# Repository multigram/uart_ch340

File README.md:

# uart_ch340
UART board using CH340C, designed with KiCAD

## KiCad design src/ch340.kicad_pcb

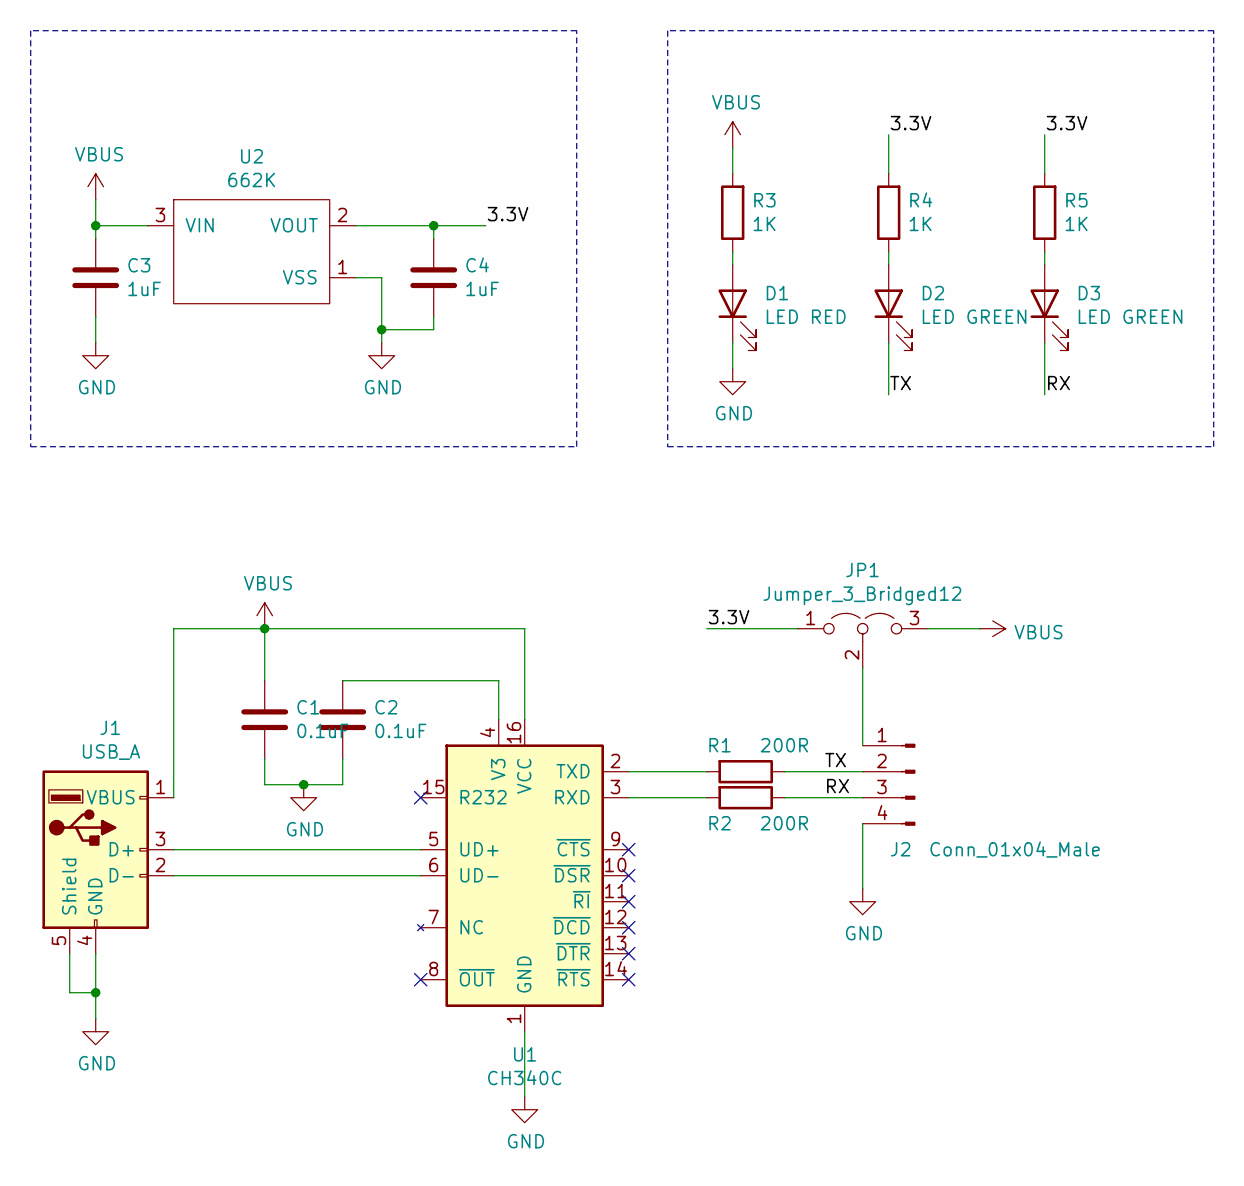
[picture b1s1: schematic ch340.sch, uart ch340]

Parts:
C1, C2: 0.1uF; C_0603_1608Metric_Pad1.08x0.95mm_HandSolder
C3, C4: 1uF; C_0603_1608Metric_Pad1.08x0.95mm_HandSolder
D1: LED RED; LED_0603_1608Metric_Pad1.05x0.95mm_HandSolder
D2, D3: LED GREEN; LED_0603_1608Metric_Pad1.05x0.95mm_HandSolder
J1: USB_A; USB_A_CNCTech_1001-011-01101_Horizontal
J2: Conn_01x04_Male; PinHeader_1x04_P2.54mm_Horizontal
JP1: Jumper_3_Bridged12; PinHeader_1x03_P2.54mm_Vertical
R1, R2: 200R; R_0603_1608Metric_Pad0.98x0.95mm_HandSolder
R3, R4, R5: 1K; R_0603_1608Metric_Pad0.98x0.95mm_HandSolder
U1: CH340C; SOIC-16_3.9x9.9mm_P1.27mm
U2: 662K; SOT-23_Handsoldering

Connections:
/3.3V: C4.1, JP1.1 (A), R4.2, R5.2, U2.2 (VOUT)
/RX: D3.1 (K), J2.3, R2.1
/TX: D2.1 (K), J2.2, R1.1
GND: C1.2, C2.2, C3.2, C4.2, D1.1 (K), J1.4 (GND), J1.5 (Shield), J2.4, U1.1 (GND), U2.1 (VSS)
unnamed: C2.1, U1.4 (V3)
unnamed: D1.2 (A), R3.1
unnamed: D2.2 (A), R4.1
unnamed: D3.2 (A), R5.1
unnamed: J1.2 (D-), U1.6 (UD-)
unnamed: J1.3 (D+), U1.5 (UD+)
unnamed: J2.1, JP1.2 (C)
unnamed: R1.2, U1.2 (TXD)
unnamed: R2.2, U1.3 (RXD)
VBUS: C1.1, C3.1, J1.1 (VBUS), JP1.3 (B), R3.2, U1.16 (VCC), U2.3 (VIN)

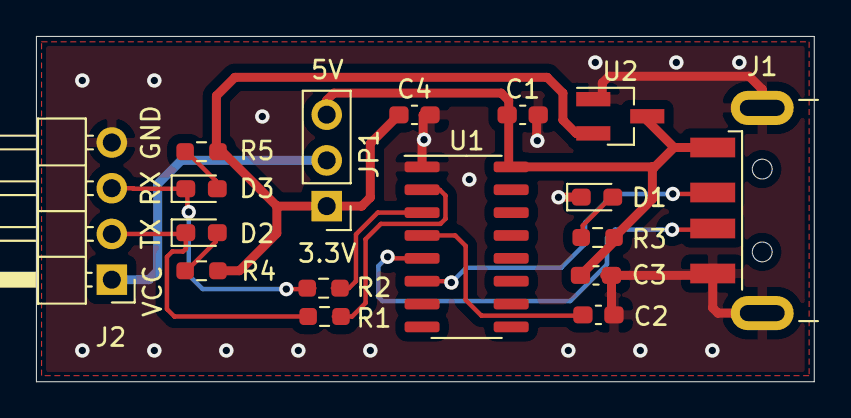
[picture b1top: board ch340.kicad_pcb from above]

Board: 2 copper layers, 43.2 x 19.2 mm, 17 parts (0 on the bottom side), 14 nets.

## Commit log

2021-06-05 add ch340c uart
2021-06-09 新增 led doc
2021-06-09 add doc/C72043_翠绿LED_2016-05-07.PDF
2021-06-18 1. set track width of GND, VCC 0.5mm 2. add vias to GND 3. change footprint, 0403 to 0603 handsoldering
2021-06-19 更新布线
2021-06-20 modify sch comment
